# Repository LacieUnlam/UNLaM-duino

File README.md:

# UNLaM-duino
Clon Arduino desarrollado en la UNLaM con KiCad, simple faz y pensado para fabricación casera.

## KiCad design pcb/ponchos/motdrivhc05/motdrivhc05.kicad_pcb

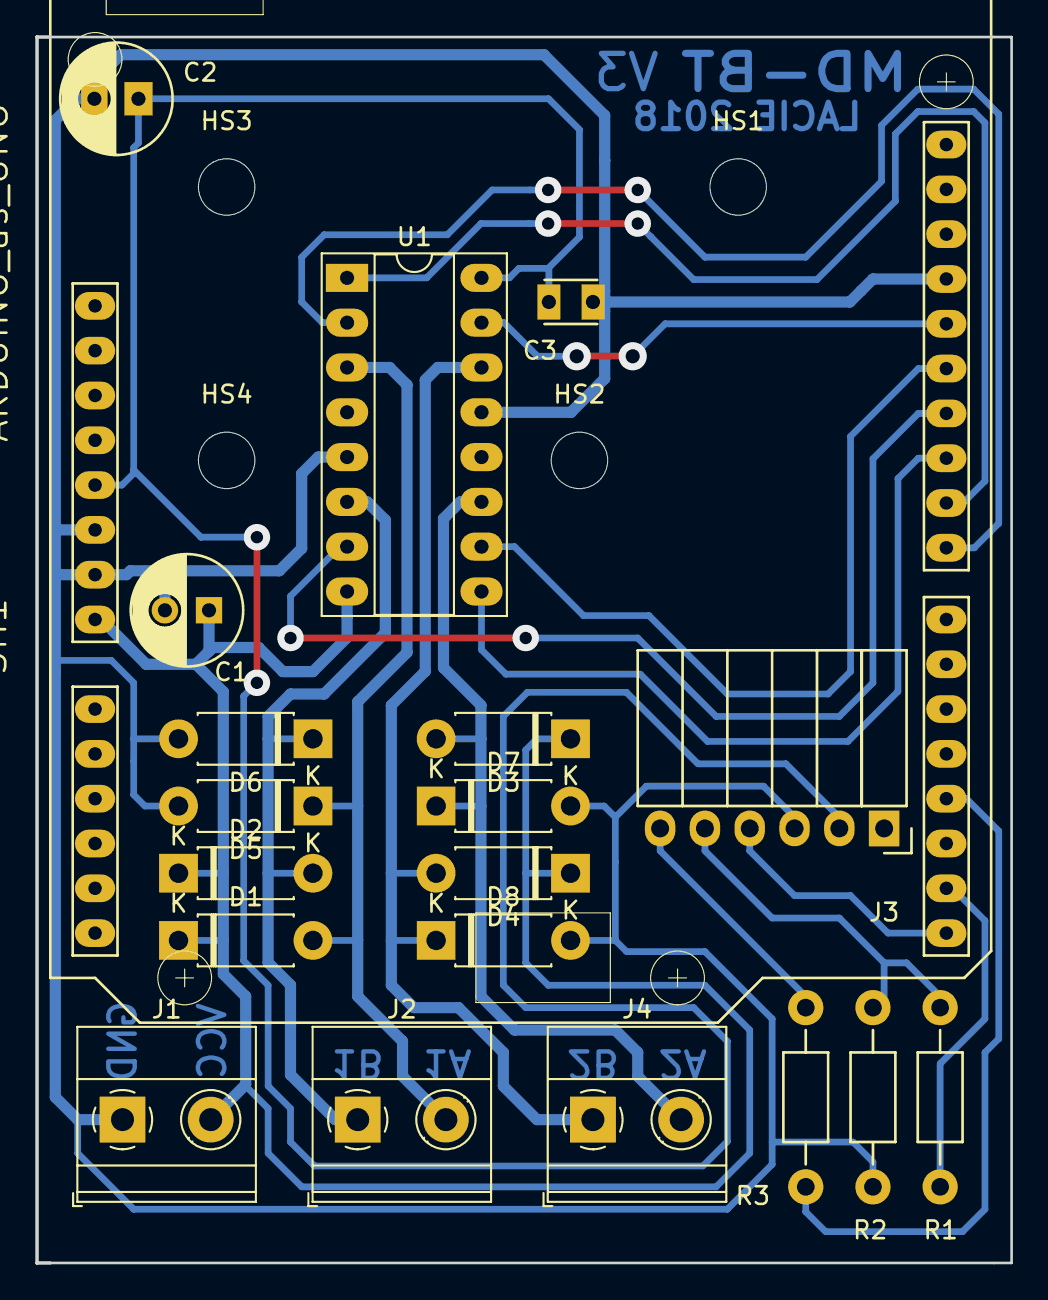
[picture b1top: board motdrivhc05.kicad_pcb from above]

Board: 2 copper layers, 55.2 x 69.5 mm, 24 parts (0 on the bottom side), 18 nets.

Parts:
C1: 47uf-50v; C_Radial_D6.3_L11.2_P2.5
C2: 100uf-6v; C_Radial_D6.3_L11.2_P2.5
C3: 100nf; C_Disc_D3_P2.5
D1, D2, D3, D4, D5, D6, D7, D8: 1N5819; D_DO-41_SOD81_P7.62mm_Horizontal
HS1, HS2, HS3, HS4: Heatsink_PAD; MountingHole_3.2mm_M3_ISO14580
J1, J2, J4: Screw_Terminal_01x02; TerminalBlock_Phoenix_MKDS-1,5-2_1x02_P5.00mm_Horizontal
J3: GW-040; Socket_Strip_Angled_1x06
R1: 1K; Resistor_Horizontal_RM10mm
R2, R3: 2K; Resistor_Horizontal_RM10mm
SH1: ARDUINO_as_UNO; ARDUINO_as_UNO_R3_CONTOUR_ELL
U1: L293; DIP-16_W7.62mm_Socket_LongPads

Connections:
+5V: C2.1, C3.1, J3.2, SH1.5V, U1.16
/1A: SH1.8, U1.2
/2A: SH1.11, U1.7
/3A: SH1.12, U1.10
/4A: SH1.13, U1.15
/BT_RXD: R1.1, SH1.1
/BT_STATE: R3.1, SH1.3
/BT_TXD: J3.4, SH1.0
/M1A: D1.2, D5.1, J2.2, U1.3
/M1B: D2.2, D6.1, J2.1, U1.6
/M2A: D3.2, D7.1, J4.2, U1.11
/M2B: D4.2, D8.1, J4.1, U1.14
/ME12: SH1.9, U1.1
/ME34: SH1.10, U1.9
GND: C1.2, C2.2, C3.2, D5.2, D6.2, D7.2, D8.2, HS2.1, HS4.1, J1.1, J3.3, R2.2, SH1.GND, U1.4, U1.5, U1.12, U1.13
unnamed: J3.5, R1.2, R2.1
unnamed: J3.6, R3.2
VCC: C1.1, D1.1, D2.1, D3.1, D4.1, J1.2, SH1.VIN, U1.8

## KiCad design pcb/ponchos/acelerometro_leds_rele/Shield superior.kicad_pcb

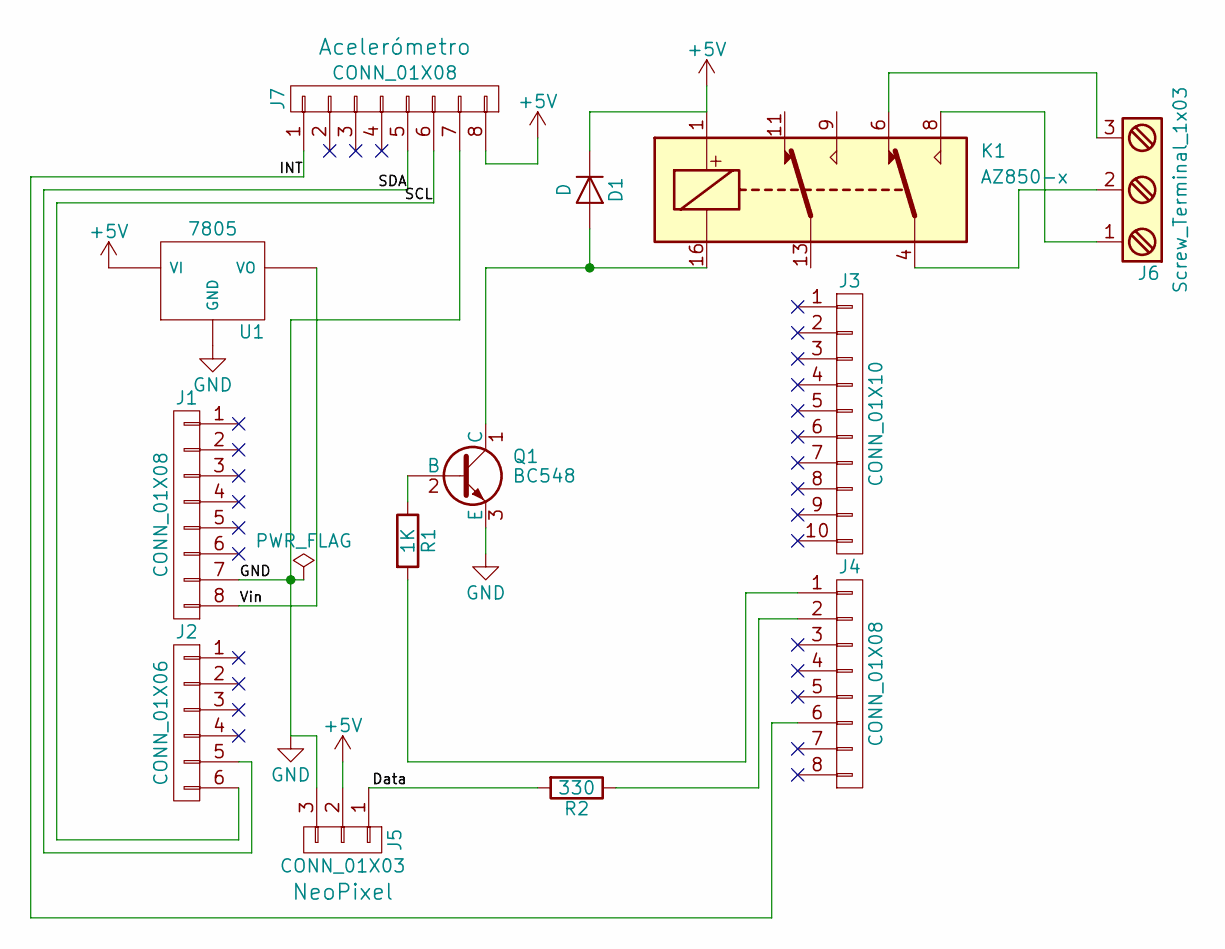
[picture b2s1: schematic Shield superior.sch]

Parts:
D1: D; D_5W_P10.16mm_Horizontal
J1, J4, J7: CONN_01X08; JST_EH_B08B-EH-A_08x2.50mm_Straight
J2: CONN_01X06; JST_EH_B06B-EH-A_06x2.50mm_Straight
J3: CONN_01X10; JST_EH_B10B-EH-A_10x2.50mm_Straight
J5: CONN_01X03; JST_EH_B03B-EH-A_03x2.50mm_Straight
J6: Screw_Terminal_1x03; TerminalBlock_Pheonix_MKDS1.5-3pol
K1: AZ850-x; Relay_THT_5V
Q1: BC548; TO-92_Inline_Wide
R1: 1K; R_Axial_DIN0207_L6.3mm_D2.5mm_P7.62mm_Horizontal
R2: 330; R_Axial_DIN0207_L6.3mm_D2.5mm_P7.62mm_Horizontal
U1: 7805; TO-92_Inline_Wide

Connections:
+5V: D1.1 (K), J5.2, J7.8, K1.1, U1.1 (VI)
/Data: J5.1, R2.2
/INT: J4.6, J7.1
/SCL: J2.6, J7.6
/SDA: J2.5, J7.5
/Vin: J1.8, U1.3 (VO)
GND: J1.7, J5.3, J7.7, Q1.3 (E), U1.2 (GND)
unnamed: D1.2 (A), K1.16, Q1.1 (C)
unnamed: J4.1, R1.2
unnamed: J4.2, R2.1
unnamed: J6.1, K1.8
unnamed: J6.2, K1.4
unnamed: J6.3, K1.6
unnamed: Q1.2 (B), R1.1

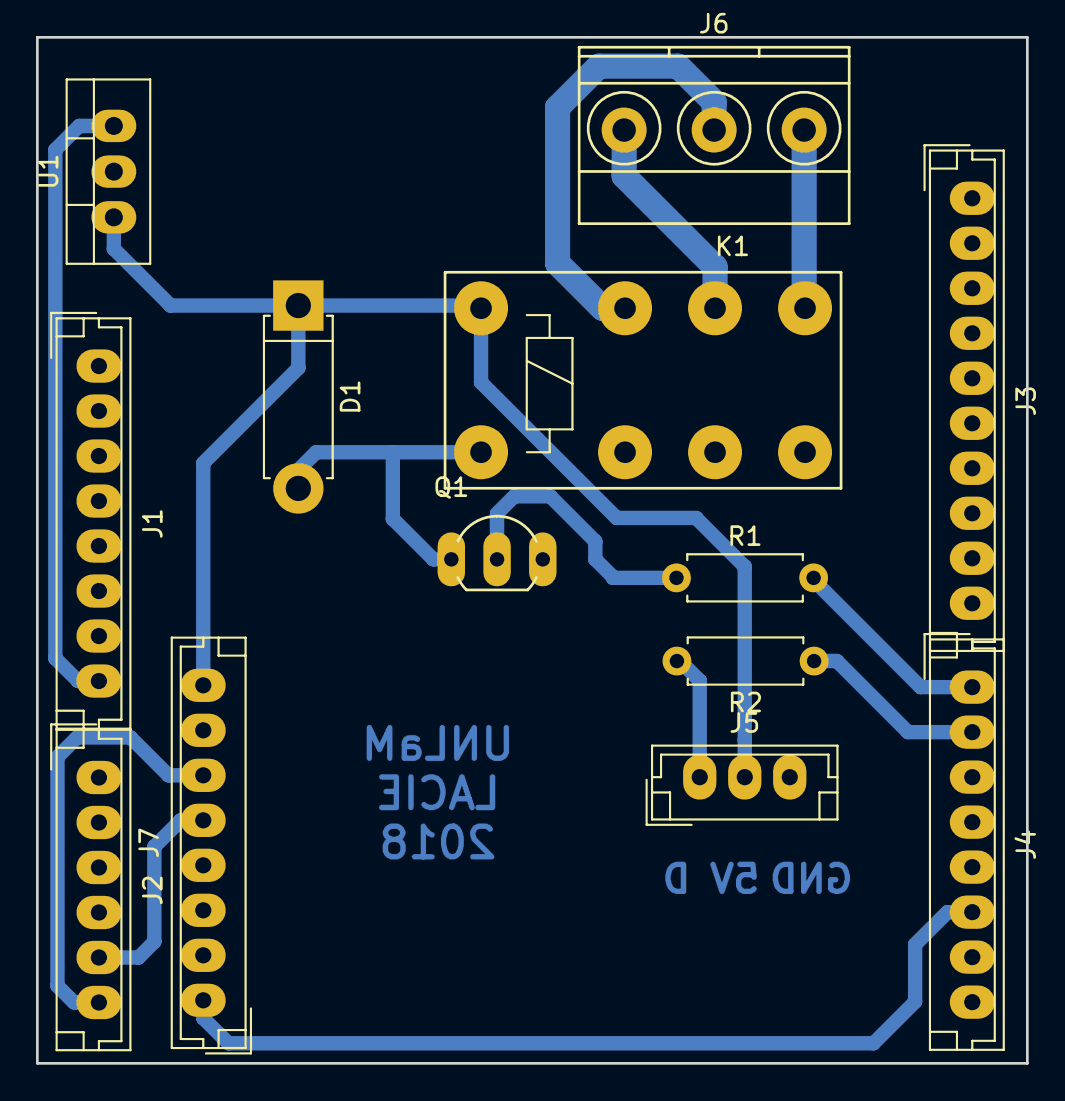
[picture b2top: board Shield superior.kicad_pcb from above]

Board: 2 copper layers, 55.0 x 57.0 mm, 13 parts (0 on the bottom side), 14 nets.

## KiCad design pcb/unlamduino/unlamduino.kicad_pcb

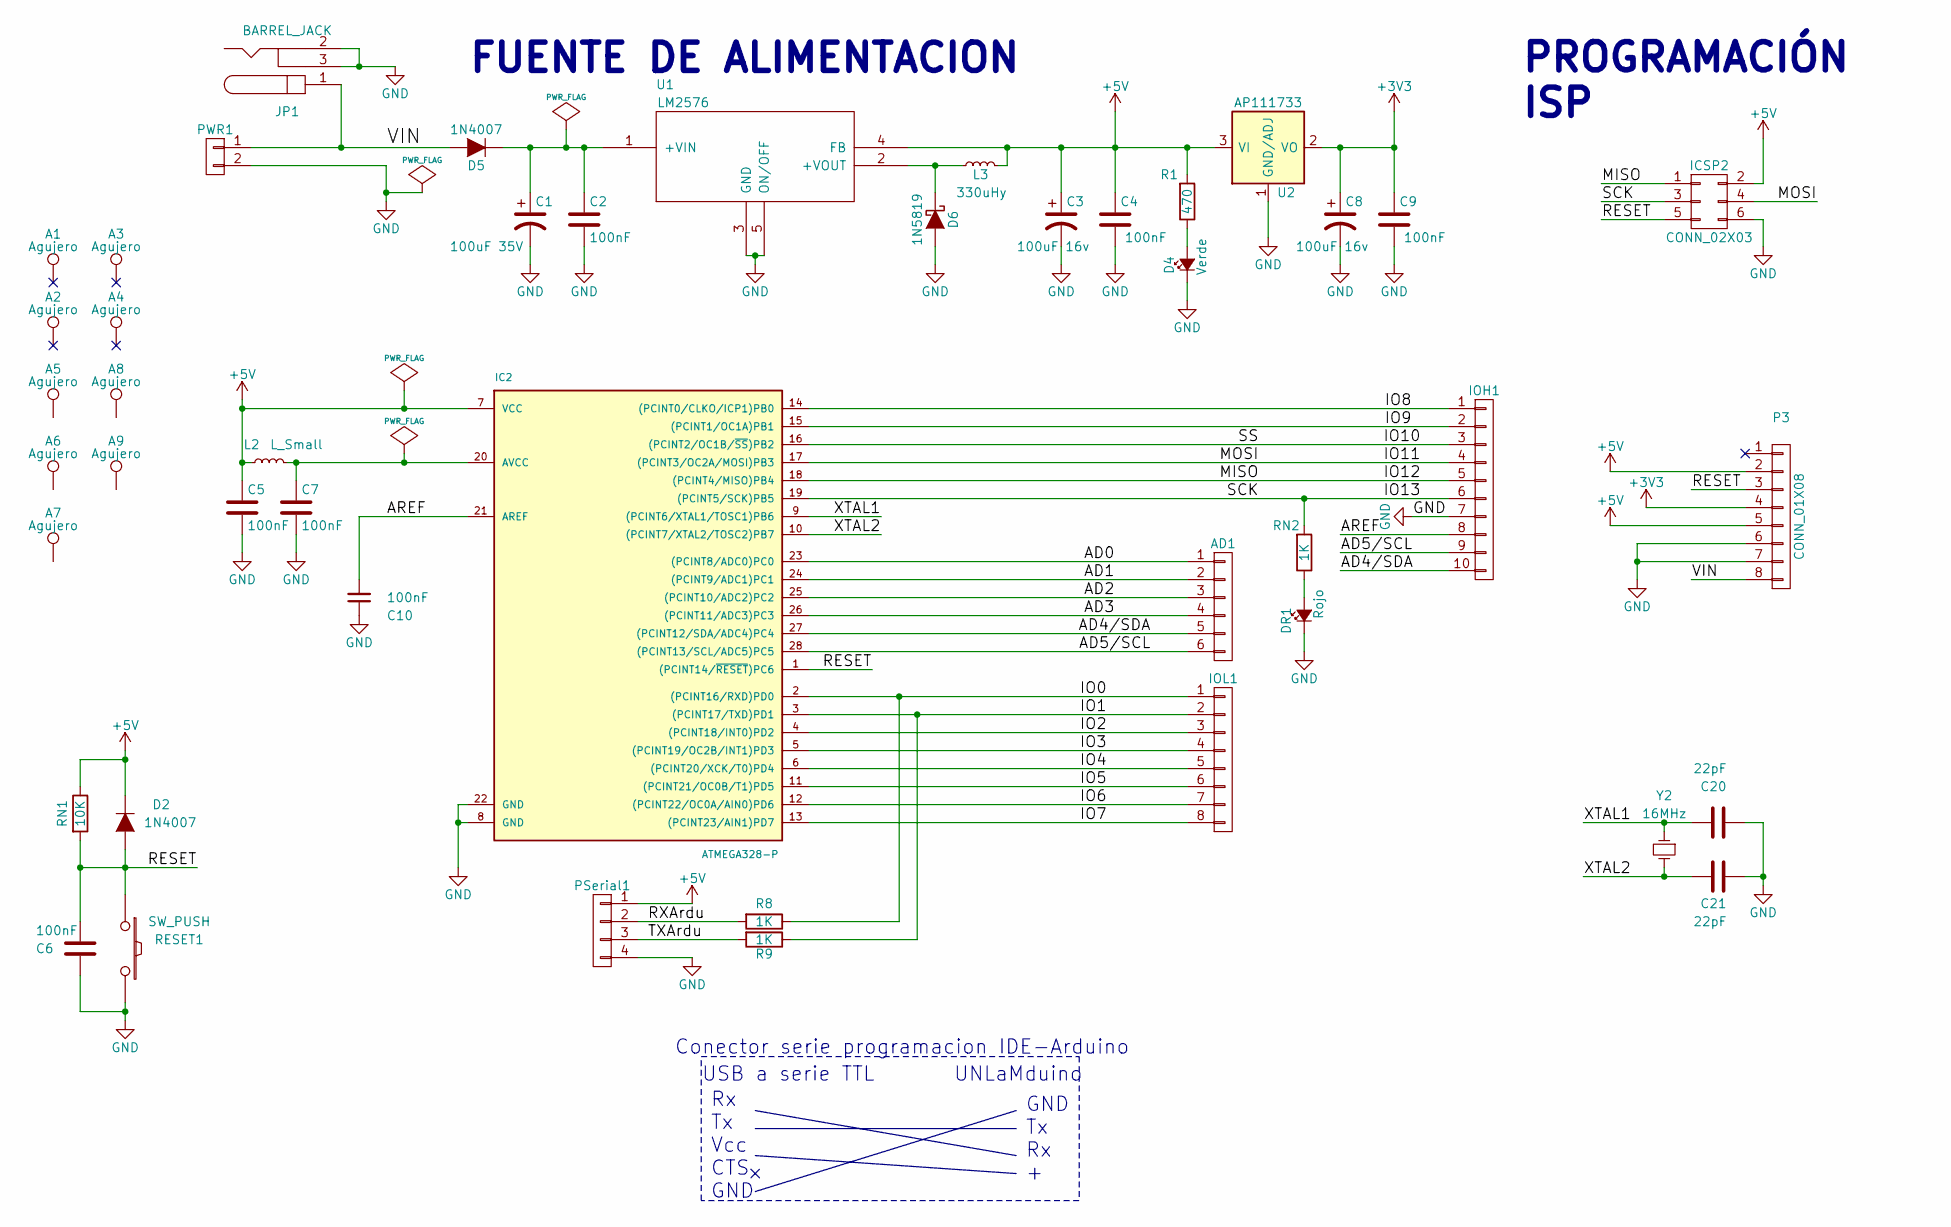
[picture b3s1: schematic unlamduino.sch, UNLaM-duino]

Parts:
A1, A2, A3, A4, A5, A6, A7, A8, A9: Agujero; MountingHole_3.2mm_M3
AD1: CONN_01X06; Pin_Header_Straight_1x06
C1: 100uF 35V; C_Radial_D6.3_L11.2_P2.5
C2, C4, C5, C6, C9, C10: 100nF; C_Disc_D3_P2.5
C3, C8: 100uF 16v; C_Radial_D6.3_L11.2_P2.5
C7: 100nF; C_Disc_D6_P5
C20, C21: 22pF; C_Disc_D3_P2.5
D2, D5: 1N4007; Diode_DO-35_SOD27_Horizontal_RM10
D4: Verde; LED-5MM
D6: 1N5819; Diode_DO-35_SOD27_Horizontal_RM10
DR1: Rojo; LED-5MM
IC2: ATMEGA328-P; DIP-28_W7.62mm_LongPads
ICSP2: CONN_02X03; Pin_Header_Straight_2x03
IOH1: CONN_01X10; Pin_Header_Straight_1x10
IOL1: CONN_01X08; Pin_Header_Straight_1x08
JP1: BARREL_JACK
L2: L_Small; Resistor_Horizontal_RM7mm3d
L3: 330uHy; INDUCTOR_V
P3: CONN_01X08; Pin_Header_Straight_1x08
PSerial1: CONN_01X04; Pin_Header_Straight_1x04
PWR1: CONN_01X02; bornier2
R1: 470; Resistor_Horizontal_RM7mm3d
R8, R9: 1K; Resistor_Horizontal_RM7mm3d
RESET1: SW_PUSH; SW_PUSH_SMALL
RN1: 10K; Resistor_Horizontal_RM7mm3d
RN2: 1K; Resistor_Horizontal_RM7mm3d
U1: LM2576; Pentawatt_Neutral_Staggered_Verical_TO220-5-T05D
U2: AP111733; TO-252-2Lead
Y2: 16MHz; Crystal_HC50-U_Vertical

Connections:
+3V3: C8.1, C9.1, P3.4, U2.2 (VO)
+5V: C3.1, C4.1, C5.1, D2.1 (K), IC2.7 (VCC), ICSP2.2, L2.1, L3.2, P3.2, P3.5, PSerial1.1, R1.2, RN1.1, U1.4 (FB), U2.3 (VI)
/AD0: AD1.1, IC2.23 ((PCINT8/ADC0)PC0)
/AD1: AD1.2, IC2.24 ((PCINT9/ADC1)PC1)
/AD2: AD1.3, IC2.25 ((PCINT10/ADC2)PC2)
/AD3: AD1.4, IC2.26 ((PCINT11/ADC3)PC3)
/AD4/SDA: AD1.5, IC2.27 ((PCINT12/SDA/ADC4)PC4), IOH1.10
/AD5/SCL: AD1.6, IC2.28 ((PCINT13/SCL/ADC5)PC5), IOH1.9
/AREF: C10.2, IC2.21 (AREF), IOH1.8
/IO0: IC2.2 ((PCINT16/RXD)PD0), IOL1.1, R8.1
/IO1: IC2.3 ((PCINT17/TXD)PD1), IOL1.2, R9.1
/IO2: IC2.4 ((PCINT18/INT0)PD2), IOL1.3
/IO3: IC2.5 ((PCINT19/OC2B/INT1)PD3), IOL1.4
/IO4: IC2.6 ((PCINT20/XCK/T0)PD4), IOL1.5
/IO5: IC2.11 ((PCINT21/OC0B/T1)PD5), IOL1.6
/IO6: IC2.12 ((PCINT22/OC0A/AIN0)PD6), IOL1.7
/IO7: IC2.13 ((PCINT23/AIN1)PD7), IOL1.8
/IO8: IC2.14 ((PCINT0/CLKO/ICP1)PB0), IOH1.1
/IO9: IC2.15 ((PCINT1/OC1A)PB1), IOH1.2
/IO10: IC2.16 ((PCINT2/OC1B/~SS~)PB2), IOH1.3
/IO11: IC2.17 ((PCINT3/OC2A/MOSI)PB3), ICSP2.4, IOH1.4
/IO12: IC2.18 ((PCINT4/MISO)PB4), ICSP2.1, IOH1.5
/IO13: IC2.19 ((PCINT5/SCK)PB5), ICSP2.3, IOH1.6, RN2.2
/RESET: C6.1, D2.2 (A), IC2.1 ((PCINT14/~RESET~)PC6), ICSP2.5, P3.3, RESET1.1, RN1.2
/RXArdu: PSerial1.2, R8.2
/TXArdu: PSerial1.3, R9.2
/VIN: D5.2 (A), JP1.1, P3.8, PWR1.1
/XTAL1: C20.1, IC2.9 ((PCINT6/XTAL1/TOSC1)PB6), Y2.1
/XTAL2: C21.1, IC2.10 ((PCINT7/XTAL2/TOSC2)PB7), Y2.2
GND: C1.2, C2.2, C3.2, C4.2, C5.2, C6.2, C7.2, C8.2, C9.2, C10.1, C20.2, C21.2, D4.2 (C), D6.2 (A), DR1.2 (C), IC2.8 (GND), IC2.22 (GND), ICSP2.6, IOH1.7, JP1.2, JP1.3, P3.6, P3.7, PSerial1.4, PWR1.2, RESET1.2, U1.3 (GND), U1.5 (ON/OFF), U2.1 (GND/ADJ)
unnamed: C1.1, C2.1, D5.1 (K), U1.1 (+VIN)
unnamed: C7.1, IC2.20 (AVCC), L2.2
unnamed: D4.1 (A), R1.1
unnamed: D6.1 (K), L3.1, U1.2 (+VOUT)
unnamed: DR1.1 (A), RN2.1

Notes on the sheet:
FUENTE DE ALIMENTACION
PROGRAMACIÓN ISP
USB a serie TTL
Rx Tx Vcc CTS GND
GND Tx Rx +
UNLaMduino
Conector serie programacion IDE-Arduino

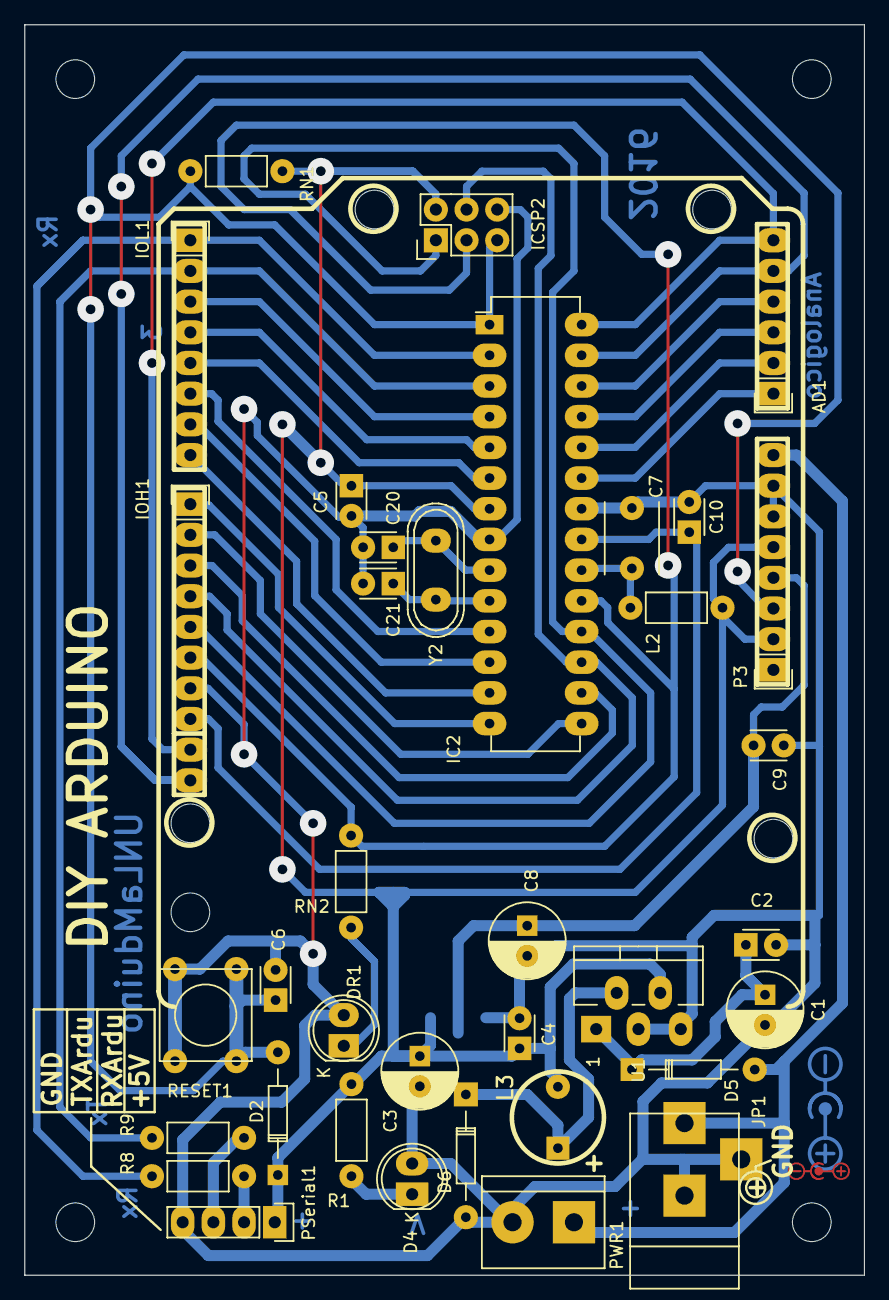
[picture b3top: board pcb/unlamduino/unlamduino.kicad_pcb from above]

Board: 2 copper layers, 69.5 x 103.5 mm, 47 parts (1 on the bottom side), 35 nets.

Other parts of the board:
Arduino_Borde: Val**; arduino_borde

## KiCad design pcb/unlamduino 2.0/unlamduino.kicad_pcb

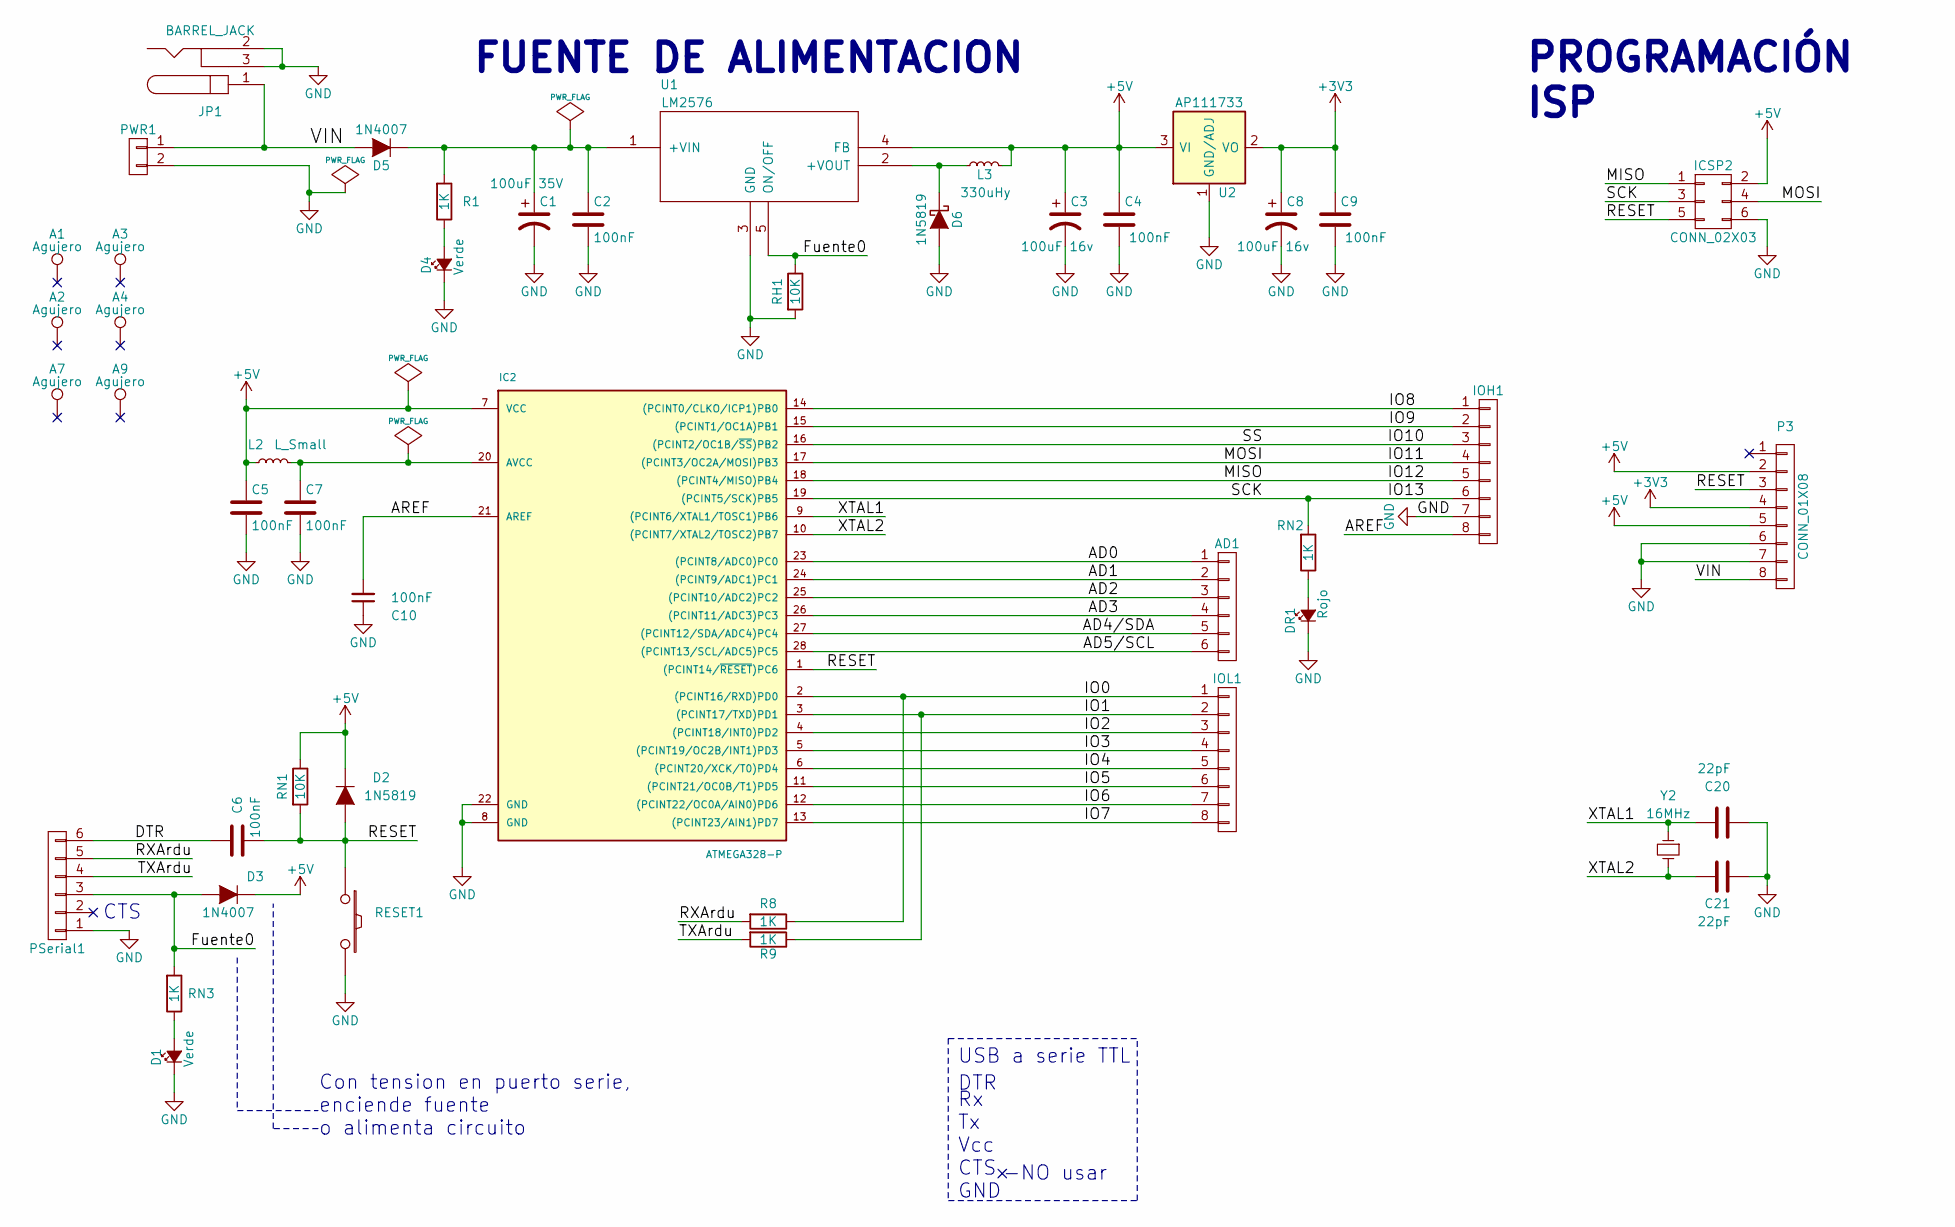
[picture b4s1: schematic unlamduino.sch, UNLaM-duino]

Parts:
A1, A2, A3, A4, A7, A9: Agujero; MountingHole_3.2mm_M3
AD1: CONN_01X06; Pin_Header_Straight_1x06
C1: 100uF 35V; C_Radial_D6.3_L11.2_P2.5
C2, C4, C5, C6, C9, C10: 100nF; C_Disc_D3_P2.5
C3, C8: 100uF 16v; C_Radial_D6.3_L11.2_P2.5
C7: 100nF; C_Disc_D6_P5
C20, C21: 22pF; C_Disc_D3_P2.5
D1, D4: Verde; LED-3MM
D2, D6: 1N5819; Diode_DO-35_SOD27_Horizontal_RM10
D3, D5: 1N4007; Diode_DO-35_SOD27_Horizontal_RM10
DR1: Rojo; LED-3MM
IC2: ATMEGA328-P; DIP-28_W7.62mm_LongPads
ICSP2: CONN_02X03; Pin_Header_Straight_2x03
IOH1: CONN_01X08; Pin_Header_Straight_1x08
IOL1: CONN_01X08; Pin_Header_Straight_1x08
JP1: BARREL_JACK
L2: L_Small; Resistor_Horizontal_RM7mm3d
L3: 330uHy; INDUCTOR_V
P3: CONN_01X08; Pin_Header_Straight_1x08
PSerial1: CONN_01X06; PINHEAD1-6
PWR1: CONN_01X02; bornier2
R1, R8, R9: 1K; Resistor_Horizontal_RM7mm3d
RESET1: SW_PUSH; SW_PUSH_SMALL
RH1: 10K; Resistor_Horizontal_RM7mm3d
RN1: 10K; Resistor_Horizontal_RM7mm3d
RN2, RN3: 1K; Resistor_Horizontal_RM7mm3d
U1: LM2576; Pentawatt_Neutral_Staggered_Verical_TO220-5-T05D
U2: AP111733; TO-252-2Lead
Y2: 16MHz; Crystal_HC50-U_Vertical

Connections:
+3V3: C8.1, C9.1, P3.4, U2.2 (VO)
+5V: C3.1, C4.1, C5.1, D2.1 (K), D3.1 (K), IC2.7 (VCC), ICSP2.2, L2.1, L3.2, P3.2, P3.5, RN1.1, U1.4 (FB), U2.3 (VI)
/AD0: AD1.1, IC2.23 ((PCINT8/ADC0)PC0)
/AD1: AD1.2, IC2.24 ((PCINT9/ADC1)PC1)
/AD2: AD1.3, IC2.25 ((PCINT10/ADC2)PC2)
/AD3: AD1.4, IC2.26 ((PCINT11/ADC3)PC3)
/AD4/SDA: AD1.5, IC2.27 ((PCINT12/SDA/ADC4)PC4)
/AD5/SCL: AD1.6, IC2.28 ((PCINT13/SCL/ADC5)PC5)
/AREF: C10.2, IC2.21 (AREF), IOH1.8; also elsewhere on the board
/DTR: C6.2, PSerial1.6; also elsewhere on the board
/Fuente0: D3.2 (A), PSerial1.3, RH1.1, RN3.2, U1.5 (ON/OFF); also elsewhere on the board
/IO0: IC2.2 ((PCINT16/RXD)PD0), IOL1.1, R8.1; also elsewhere on the board
/IO1: IC2.3 ((PCINT17/TXD)PD1), IOL1.2, R9.1; also elsewhere on the board
/IO2: IC2.4 ((PCINT18/INT0)PD2), IOL1.3; also elsewhere on the board
/IO3: IC2.5 ((PCINT19/OC2B/INT1)PD3), IOL1.4; also elsewhere on the board
/IO4: IC2.6 ((PCINT20/XCK/T0)PD4), IOL1.5; also elsewhere on the board
/IO5: IC2.11 ((PCINT21/OC0B/T1)PD5), IOL1.6; also elsewhere on the board
/IO6: IC2.12 ((PCINT22/OC0A/AIN0)PD6), IOL1.7; also elsewhere on the board
/IO7: IC2.13 ((PCINT23/AIN1)PD7), IOL1.8; also elsewhere on the board
/IO8: IC2.14 ((PCINT0/CLKO/ICP1)PB0), IOH1.1; also elsewhere on the board
/IO9: IC2.15 ((PCINT1/OC1A)PB1), IOH1.2; also elsewhere on the board
/IO10: IC2.16 ((PCINT2/OC1B/~SS~)PB2), IOH1.3; also elsewhere on the board
/IO11: IC2.17 ((PCINT3/OC2A/MOSI)PB3), ICSP2.4, IOH1.4; also elsewhere on the board
/IO12: IC2.18 ((PCINT4/MISO)PB4), ICSP2.1, IOH1.5; also elsewhere on the board
/IO13: IC2.19 ((PCINT5/SCK)PB5), ICSP2.3, IOH1.6, RN2.2; also elsewhere on the board
/RESET: C6.1, D2.2 (A), IC2.1 ((PCINT14/~RESET~)PC6), ICSP2.5, P3.3, RESET1.1, RN1.2; also elsewhere on the board
/RXArdu: PSerial1.5, R8.2; also elsewhere on the board
/TXArdu: PSerial1.4, R9.2; also elsewhere on the board
/VIN: D5.2 (A), JP1.1, P3.8, PWR1.1
/XTAL1: C20.1, IC2.9 ((PCINT6/XTAL1/TOSC1)PB6), Y2.1
/XTAL2: C21.1, IC2.10 ((PCINT7/XTAL2/TOSC2)PB7), Y2.2
GND: C1.2, C2.2, C3.2, C4.2, C5.2, C7.2, C8.2, C9.2, C10.1, C20.2, C21.2, D1.2 (C), D4.2 (C), D6.2 (A), DR1.2 (C), IC2.8 (GND), IC2.22 (GND), ICSP2.6, IOH1.7, JP1.2, JP1.3, P3.6, P3.7, PSerial1.1, PWR1.2, RESET1.2, RH1.2, U1.3 (GND), U2.1 (GND/ADJ); also elsewhere on the board
unnamed: C1.1, C2.1, D5.1 (K), R1.2, U1.1 (+VIN)
unnamed: C7.1, IC2.20 (AVCC), L2.2
unnamed: D1.1 (A), RN3.1
unnamed: D4.1 (A), R1.1
unnamed: D6.1 (K), L3.1, U1.2 (+VOUT)
unnamed: DR1.1 (A), RN2.1

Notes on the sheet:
FUENTE DE ALIMENTACION
PROGRAMACIÓN ISP
USB a serie TTL
CTS
Rx Tx Vcc CTS GND
-NO usar
DTR
Con tension en puerto serie, enciende fuente o alimenta circuito

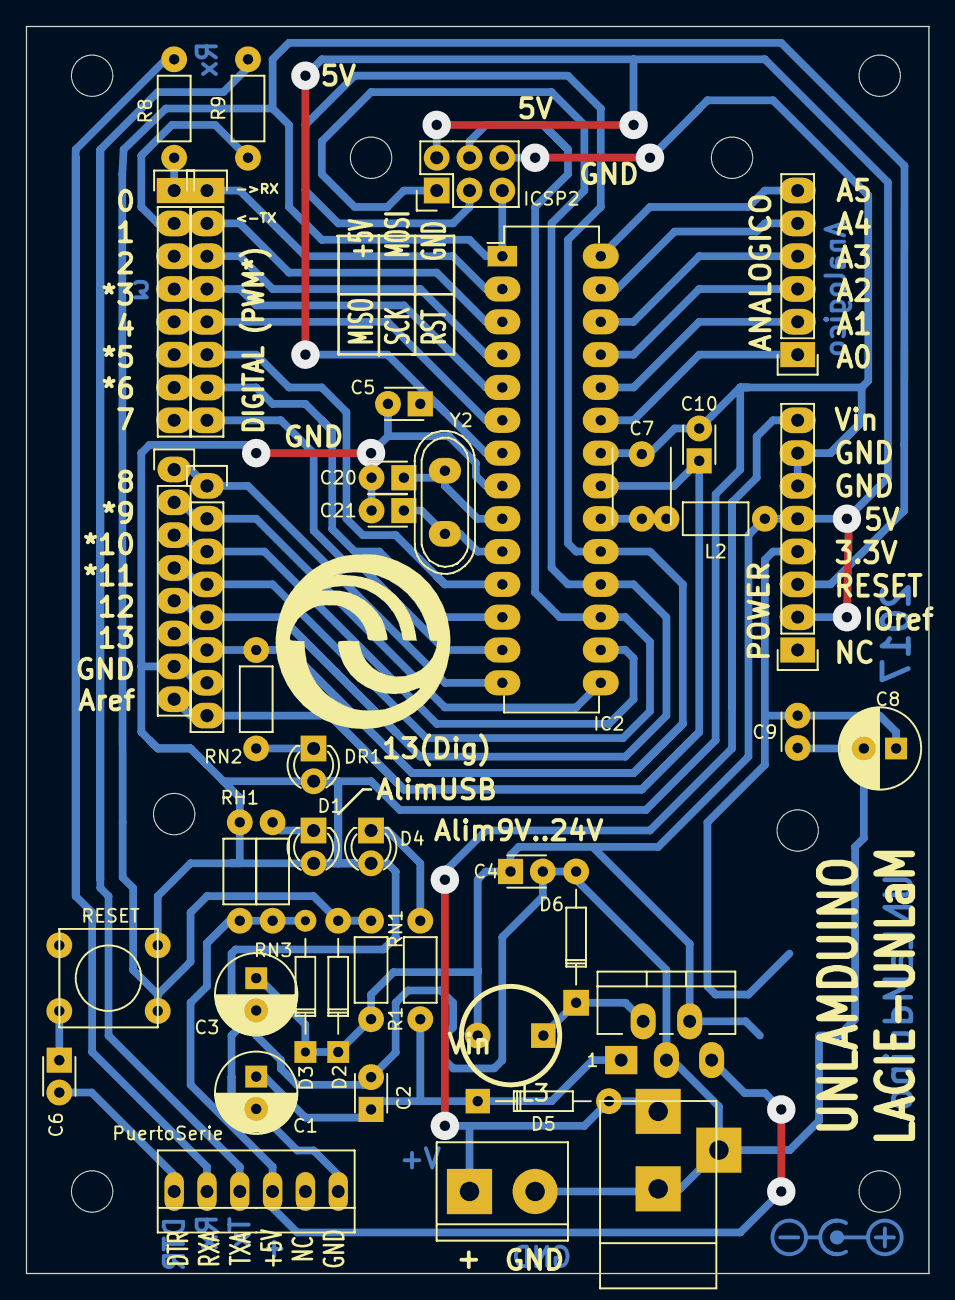
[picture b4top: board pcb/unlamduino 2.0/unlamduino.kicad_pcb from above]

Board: 2 copper layers, 69.8 x 96.5 mm, 51 parts (1 on the bottom side), 38 nets.

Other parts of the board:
A5, A6, A8: Agujero; MountingHole_3.2mm_M3
IOH1#2: CONN_01X08; Pin_Header_Straight_1x08
IOL1#2: CONN_01X08; Pin_Header_Straight_1x08
PuertoSerie: CONN_01X06; PINHEAD1-6
RESET: SW_PUSH; SW_PUSH_SMALL

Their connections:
/AREF: IOH1#2.8; also elsewhere on the board
/DTR: PuertoSerie.6; also elsewhere on the board
/Fuente0: PuertoSerie.3; also elsewhere on the board
/IO0: IOL1#2.1; also elsewhere on the board
/IO1: IOL1#2.2; also elsewhere on the board
/IO2: IOL1#2.3; also elsewhere on the board
/IO3: IOL1#2.4; also elsewhere on the board
/IO4: IOL1#2.5; also elsewhere on the board
/IO5: IOL1#2.6; also elsewhere on the board
/IO6: IOL1#2.7; also elsewhere on the board
/IO7: IOL1#2.8; also elsewhere on the board
/IO8: IOH1#2.1; also elsewhere on the board
/IO9: IOH1#2.2; also elsewhere on the board
/IO10: IOH1#2.3; also elsewhere on the board
/IO11: IOH1#2.4; also elsewhere on the board
/IO12: IOH1#2.5; also elsewhere on the board
/IO13: IOH1#2.6; also elsewhere on the board
/RESET: RESET.1; also elsewhere on the board
/RXArdu: PuertoSerie.5; also elsewhere on the board
/TXArdu: PuertoSerie.4; also elsewhere on the board
GND: IOH1#2.7, PuertoSerie.1, RESET.2; also elsewhere on the board

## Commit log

2016-07-13 Agrego información sobre el Severino.
2016-08-27 Agrego readme básico ide arduino.
2016-09-08 Maq de Estados para AVRRobot.
2016-09-10 Agregado de comunicacion serie del robot a la PC para DEBUG
2016-09-10 Diagrama de la máquina de estados implementada.
2016-09-10 Tutorial de instalación de Arduino
2016-09-12 Cambios menores en la estética, motivos de salida más cerca de la flecha.
2016-09-12 Uso de tiempo tomado por el objeto y cambio en deshabilitacion del motor que estaba erroneo.
2016-09-19 Comentarios respecto a la función de cada pin más detallados.
2016-09-19 Comentarios más descriptivos, mejora en el tipo de letra del diagrama.
2016-09-19 Corrección de estado Avanzar.
2016-09-19 Cambio de nombre
2016-09-24 Agregado de un estado "DUMMY" para que no de error el IDE 1.6.X
2016-09-24 Agregado de comentarios del programador
2016-09-28 Agregado de Salida de Código para luces.
2016-09-28 Cambio de nombre de las partes del estado, intentando hacerlo más legible.
2016-09-28 Agregado de comandos disponible para LEDs.
2016-09-29 Comentado, la posibilidad de PWM de los motores. Cambio de definición de los motores en un solo lugar.
2016-09-29 Agregado de dirección de cada motor definido en el pin de cada motor.
2016-09-29 LED que titila mientras está en la espera.
2016-09-30 Agrego información sobre Ktuluino.
2016-10-04 Agregado de Latido en LED1 (Estado Victoria).
2016-10-05 Comienzo de nuestra versión del Arduino, PCB para hacer con la plancha, usar USB-SerieTTL
2016-10-05 Reorganizo nombres.
2016-10-05 Quito librerias.
2016-10-05 Agregado PWR_FLAG y numeracion. Agregado de valores a algunos capacitores.
2016-10-06 Agregado regulador de 3v3 y conectores a utilizar.
2016-10-06 Resistor en led de encendido de 470 en vez de 2 de 1K
2016-10-08 Primera asignacion de encapsulados a las partes del circuito.
2016-10-08 Netlist con todos los encapsulados definidos.
2016-10-08 Preliminar de posición de componentes en la placa.
2016-10-08 PCB inicial
2016-10-08 cache que me olvide
2016-10-19 Colocacion en plantilla de conectores, alineados con grilla de 25, los que se pueden.
2016-10-19 Modificacion de tamaño de componentes, achicados y más reales.
2016-10-19 Acomodamiento preliminar de componentes, sin fuente 3v3
2016-10-20 Añadido de agujeros M3 como en el Arduino original, ruteo preliminar con 10 puentes.
2016-10-20 Agujeros de 3mm
2016-10-20 Agujeros de fijación
2016-10-20 Ruteo en 0,6mm de pista para hacer una aproximación al definitivo.
    Eliminación del puente de reset. Reacomodamiento de resistor de reset.
    Ver capa de reset que quedó en el pulsador.
2016-10-22 Acomodado de componentes para mejorar ruteo, minimización de pistas faltantes.
2016-10-22 Re-acomodo de la fuente y consolidacion de 8 puentes. Relleno de zonas.
2016-10-22 Elección Xtal con pisada correcta.
2016-10-22 Corrección agujeros de montaje.
2016-10-22 Cambio de ancho en algunas pistas.
2016-10-22 Pistas gruesas en fuente, cambio de agujeros de fijación a los que dice el sch
2016-10-22 Dibujo del borde de la placa.
2016-10-22 Agregado de texto indicador de Montajes y diseño. Patas 1 de los integrados
2016-10-22 Coincidencia del orden del conector 8 a 13 con los pines de la regleta.
2016-10-22 Acomodado de serigrafía
2016-10-22 Acomodado de algunos textos.
2016-10-22 Corrección separación de patas del inductor de la fuente.
2016-10-31 Separación de pistas, añadido de puente para mejorar planchado.
2016-10-31 cambio de 5v en conector para no pasar por el medio de un capa.
2016-11-02 Ajuste de la fuente a la nueva distribución de pistas para planchar.
2016-11-02 Agregado agujeros de fijación y borde de relleno.
2016-11-02 Correccion de algunas pistas cerca de islas y limpieza de pistas solapadas.
2016-11-02 Cambio separacion de patas de C7
2016-11-02 Capacitor mas ancho por pista por el medio y acomodado de alguna pista.
2016-11-03 Conector de alimentacion corrido para lugar de agujero.
2016-11-04 unlamduino.sch: Agregu agujeros faltantes, quito etiqueta 5V, leyenda ISP, detalles de uniones.
2016-11-04 Agrego biblioteca local huellas.pretty con los footprints del unlamduino.
2016-11-04 unlamduino pcb: Ordeno serigrafía. Coloco borde adecuado. Muevo límite de zona de relleno. Numero aducuadamente los agujeros.
2016-11-04 Agrego footprint del inductor.
2016-11-04 Cambio el footprint asociado del inductor de fuente del unlamduino.
2016-11-04 PCB Unlamduino: Muevo componentes para que no se superpomgam. Ubico L1 con su nuevo footprint. Subo o el margen a 0,5 mm. Corrijo varias pistas cerca. Aún pendientes C21, C20, L2, IOH1.
2016-11-05 Unlamduino .sch: cambio footprint del inductor del A/D por uno más chico 10mm a 7mm.
2016-11-05 Unlamduino pcb: Muevo los componentes superpuestos. Quito errores DRC para 0,5mm. Agrego textos y aclaraciones a la serigrafía.
2016-11-05 Unlamduino: Agrego huellas de arduino para serigrafía y verificación.
2016-11-05 Agrego señales rx y tx en el conector serie para identificar en el PCB.
2016-11-05 Detalles de ruteo, serigrafía de borde de Arduino, Indicaciones en la serigrafía.
2016-11-05 Agrego modelos 3D para el Unlamduino.
2016-11-05 Agrego modelos 3d del unlamduino.
2016-11-05 Completo vista 3D
2016-11-05 Agrego huella resistor RM7mm con info de modelo 3d.
2016-11-05 Unlamduino: Leds 3d en colores.
2016-11-05 Limpieza de pistas huérfanas y de 2 segmentos. Agrandado de islas para mejor planchado.
2016-11-05 Uniformado de diametro de agujeros.
2016-11-05 Corrijo algunas rutas 3D.
2016-11-05 Girado de integrado de la fuente, para poder acostarlo.
2016-11-05 Cambios en tamaño de islas para pines.
2016-11-05 Agregado logo en cobre de polaridad de fuente externa.
2016-11-26 Cambio de conector de alimentacion que estaba erroneo.
2016-11-26 Añadido de biblioteca con simbolo de polaridad de conector.
2016-11-26 Añadido de simbolo de polaridad, orientacion para no desperdiciar papel, corrección de conector.
2016-11-26 biblioteca de simbolo de polaridad.
2016-11-26 Añadido de simbolo de polaridad al proyecto.
2016-11-26 Añadido de logos.
2016-12-03 cambio huella de regulador de 3v3. Marca Tx y Rx cerca conector.
2016-12-03 Agregado de la definición del cable serie para programar en niveles TTL.
2016-12-03 Trazado de pista en pata central para compatibilidad con SOT de 4 patas.
2017-08-23 Inicio del proyecto de poncho motdrivhc05.
2017-08-24 Iniciando el esquemático del poncho. Modificado del L293 y guardado en nueva lib por errores en la lib original kicad.
2017-08-26 En proceso esquemático...
2017-08-28 En proceso...
2017-08-29 Creado componente de librería del modulo Bluetooth GW-040.
2017-08-30 Correciónes del componente esquemático Arduino shield. Finalizada propuesta de esquemático. PCB en desarrollo.
2017-08-31 Haciendo PCB...
2017-09-02 En desarrollo...
2017-09-04 En processo...
2017-09-05 Primer versión de PCB terminada.
2017-09-06 Correcciones de serigrafía. Correcciones sobre algunos detalles en pistas.
2017-09-07 Agregado comentarios en PCB.
2017-09-12 Reordenado de serigrafía.
2017-09-13 Agregado y modificado de nombres de nets en esquemático. Agregado de serigrafías con referencias en PCB.
2017-09-23 Comienzo de version 2
2017-09-23 Reorganizacion de la fuente
2017-09-23 Corregido error en disposición de pines de módulo bluetooth, y correción en PCB.
2017-09-28 Desplazadas pineras shield arduino. Agregado de serigrafía en capa cobre de datos de laboratorio y versión de la placa. Corregido 3D shape del conector de bluetooth.
2017-10-14 Algunas correciones varias. Desplazamiento del conector de motores, para que no interfieran las soldaduras con el conector SPI de arduino.
2017-11-25 Nueva placa mejor distribuida.
2017-11-25 Cambios minimos, limpieza de trazos redundantes y movimineto de algunas pistas para maximizar llenado.
2017-12-02 Mejoras esteticas, cambio de serigrafía, alineacion de R y diodos, instrucciones en cobre.
2017-12-02 Correccion de agujeros de fijacion. Y en el esquematico conexion del adaptador USB-serie.
2018-06-09 Agrego fotos del unlamduino.
2018-06-09 Agrego fotos del shield de motores.
2018-06-09 Agrego fotos arduino y shield juentos.
2018-07-07 Conector de programacion completo.
2018-07-07 Controlador puente H con ejemplo y cambios menores en pistas (limpieza de pista huérfanas).
2018-07-07 añadido de archivo ZIP de biblioteca de control de motor por puente H.
2018-07-07 agrego presentacion de la actividad de futbol robot.
2018-07-07 Agregado la info de Neopixel de German Cardozo.
2018-08-23 Corrimiento del conector, agujeros para disipador, giro capacitores para poner acostados, cambio pin del key/status, se quitó el transistor para rele.
2018-08-25 Subo el margen de 0,2 a 0,4 y corrijo algunas distancias. Faltan unas pocas más.
2018-08-25 Modelos 3D relativos al proyecto. Foto en el README.md.
2018-09-05 Shield de motores plano, con mayor margen.
2018-09-05 Agrego para imprimir 3 shields.
2018-09-05 Se ensancharon algunas pistas.
2018-09-05 Agrego hoja para imprimir de a 6 placas.
2018-09-06 Ensancho vías y agujeros.
2018-09-06 Agrego pdfs generados.
2018-09-08 Correción de archivo notas. Agregada carpeta con demo y librerías.
2018-09-27 Agrego primera version Shield acelerometro, rele y neopixel. Falta detalle de posicion de conector arduino y correr conector de acelerometro.
2018-09-29 Agrego ejemlos del Shield de Neopixel+Relé+Acelerómetros, verifiados por Spinazola.
2018-10-04 Correción del demo original de control de motores. Correción en PBC.
2018-10-05 Modificaciones al shield superior, mejora en conexión del acelerómetro y ajueste de distancias en el ponout del arduino.
2018-10-06 Agrego para imprimir placas.
2018-10-06 Agrego primer programa de futbot curso 2018. Motores y luces con BT.
2018-10-10 Agrego APK de Appugliese.
2018-10-11 Modifico para agrandar margen a 0,6 huellas y símbolos dentro del proyecto.
2018-10-11 Detalle borde de pcb y cotas.
2018-10-11 Pads mas grandes para el transistor.
2018-10-11 Agrego impresion de varios shields por hoja.
2018-10-18 Ajustes de variales en FutbolRobot_0-3.ino.
2018-10-20 Renombrado del fichero según exigencia de la IDE Arduino.
2018-11-13 motdrivhc05: -Migración a Kicad 5. -Eliminación de varios puentes, algunos que podían hacer contacto con el módulo bluetooth. -Vinculado pin Vin de Arduino con linea de VCC. -Bloques de terminales en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
2018-11-15 motdrivhc05: -Correción en la especificación de orificios.
2019-09-16 Agrego instructivo para cambiar nombre y clave de los HC-05 y los HC-06.
2019-09-16 Aclaraciones y urls usadas.
